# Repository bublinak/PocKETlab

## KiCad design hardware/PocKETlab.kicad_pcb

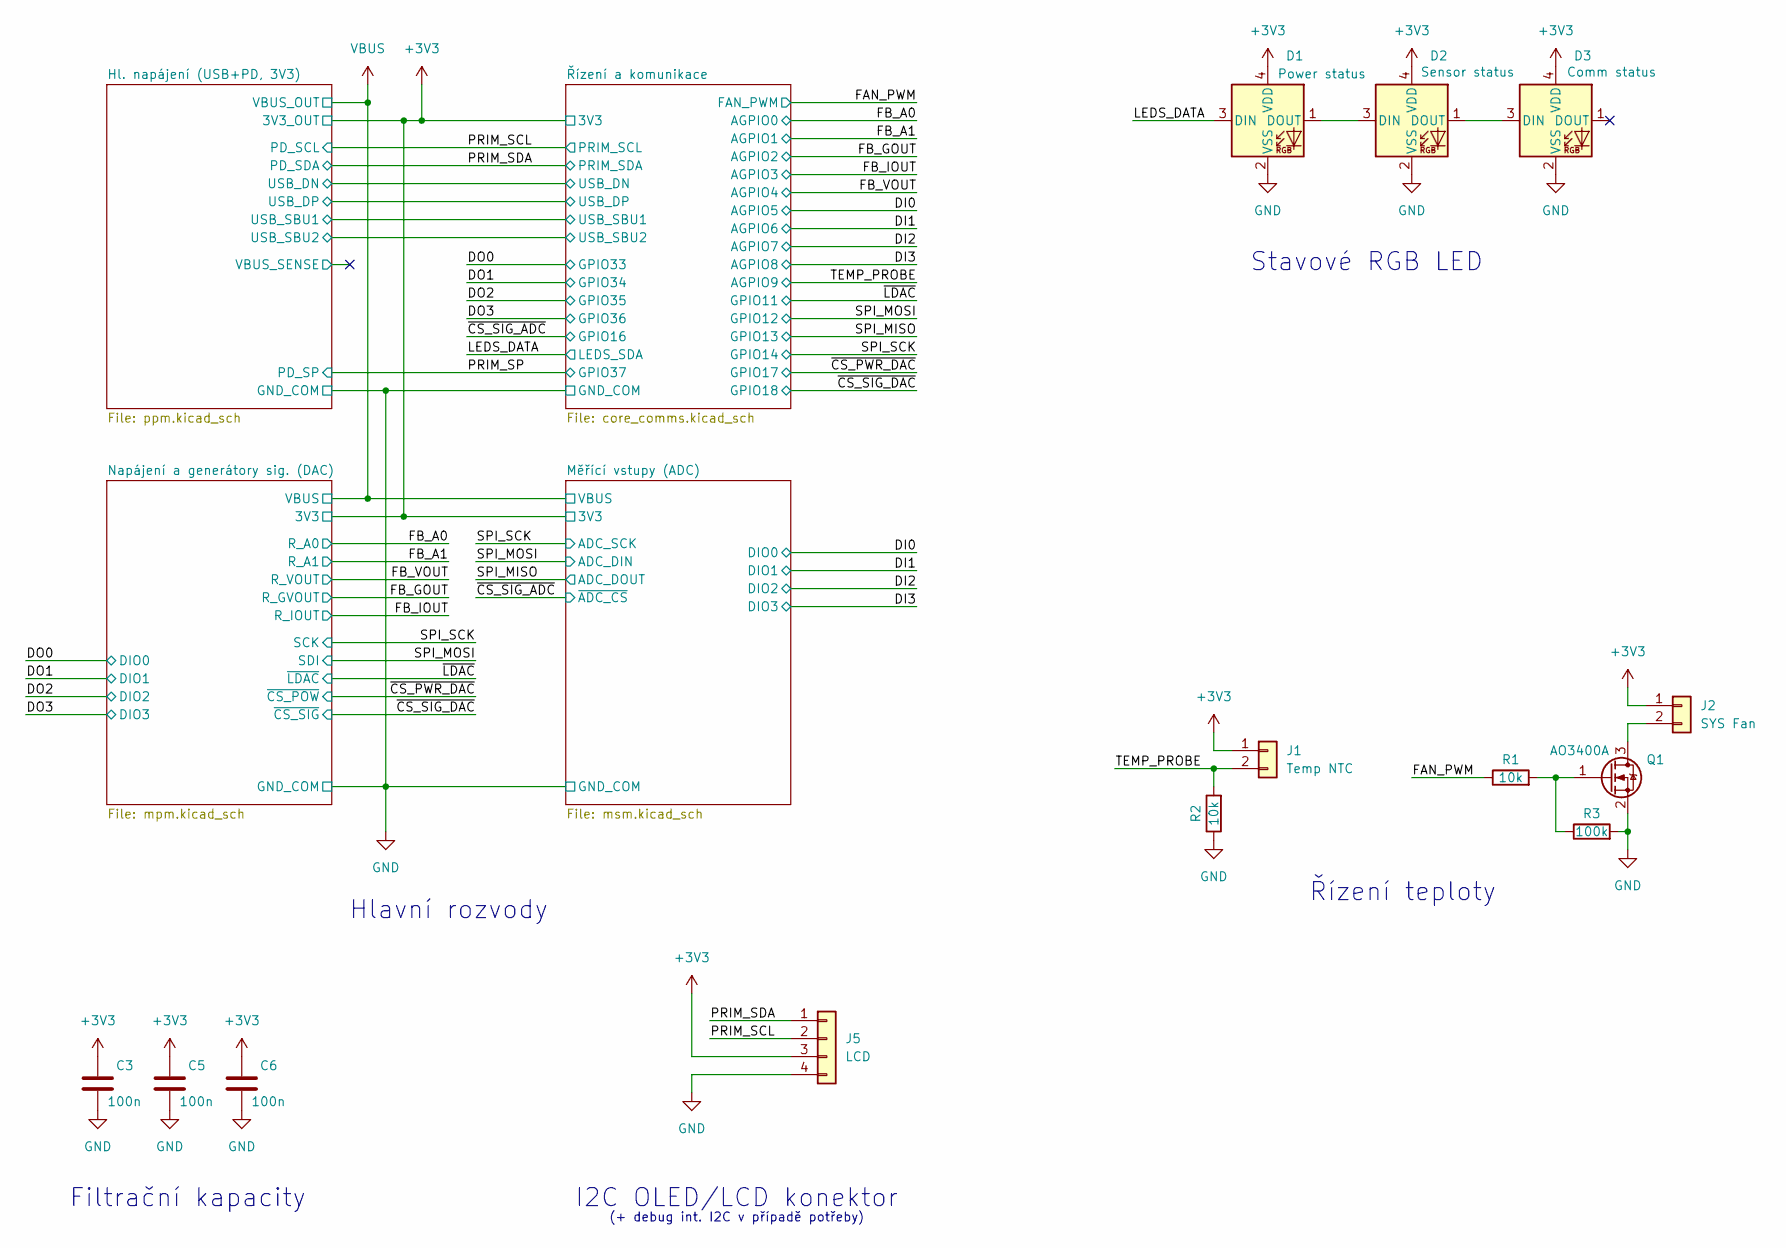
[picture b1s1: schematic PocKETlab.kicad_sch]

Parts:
C3, C5, C6: 100n; C_0603_1608Metric; LCSC Part C14663
D1: Power status; LED_WS2812B-2020_PLCC4_2.0x2.0mm; LCSC Part C5349955
D2: Sensor status; LED_WS2812B-2020_PLCC4_2.0x2.0mm; LCSC Part C5349955
D3: Comm status; LED_WS2812B-2020_PLCC4_2.0x2.0mm; LCSC Part C5349955
J1: Temp NTC; JST_PH_B2B-PH-K_1x02_P2.00mm_Vertical
J2: SYS Fan; JST_PH_B2B-PH-K_1x02_P2.00mm_Vertical
J5: LCD; JST_PH_B4B-PH-K_1x04_P2.00mm_Vertical
Q1: AO3400A; SOT-23; LCSC Part C20917
R1, R2: 10k; R_0603_1608Metric; LCSC Part C25804
R3: 100k; R_0603_1608Metric; LCSC Part C15458

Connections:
+3V3: C3.1, C5.1, C6.1, D1.4 (VDD), D2.4 (VDD), D3.4 (VDD), J1.1, J2.1, J5.3; also elsewhere on the board
/FAN_PWM: R1.1; also elsewhere on the board
/LEDS_DATA: D1.3 (DIN); also elsewhere on the board
/PRIM_SCL: J5.2; also elsewhere on the board
/PRIM_SDA: J5.1; also elsewhere on the board
/TEMP_PROBE: J1.2, R2.2; also elsewhere on the board
GND: C3.2, C5.2, C6.2, D1.2 (VSS), D2.2 (VSS), D3.2 (VSS), J5.4, Q1.2 (S), R2.1, R3.2; also elsewhere on the board
unnamed: D1.1 (DOUT), D2.3 (DIN)
unnamed: D2.1 (DOUT), D3.3 (DIN)
unnamed: J2.2, Q1.3 (D)
unnamed: Q1.1 (G), R1.2, R3.1

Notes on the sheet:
Hlavní rozvody
Řízení teploty
(+ debug int. I2C v případě potřeby)
I2C OLED/LCD konektor
Stavové RGB LED
Filtrační kapacity

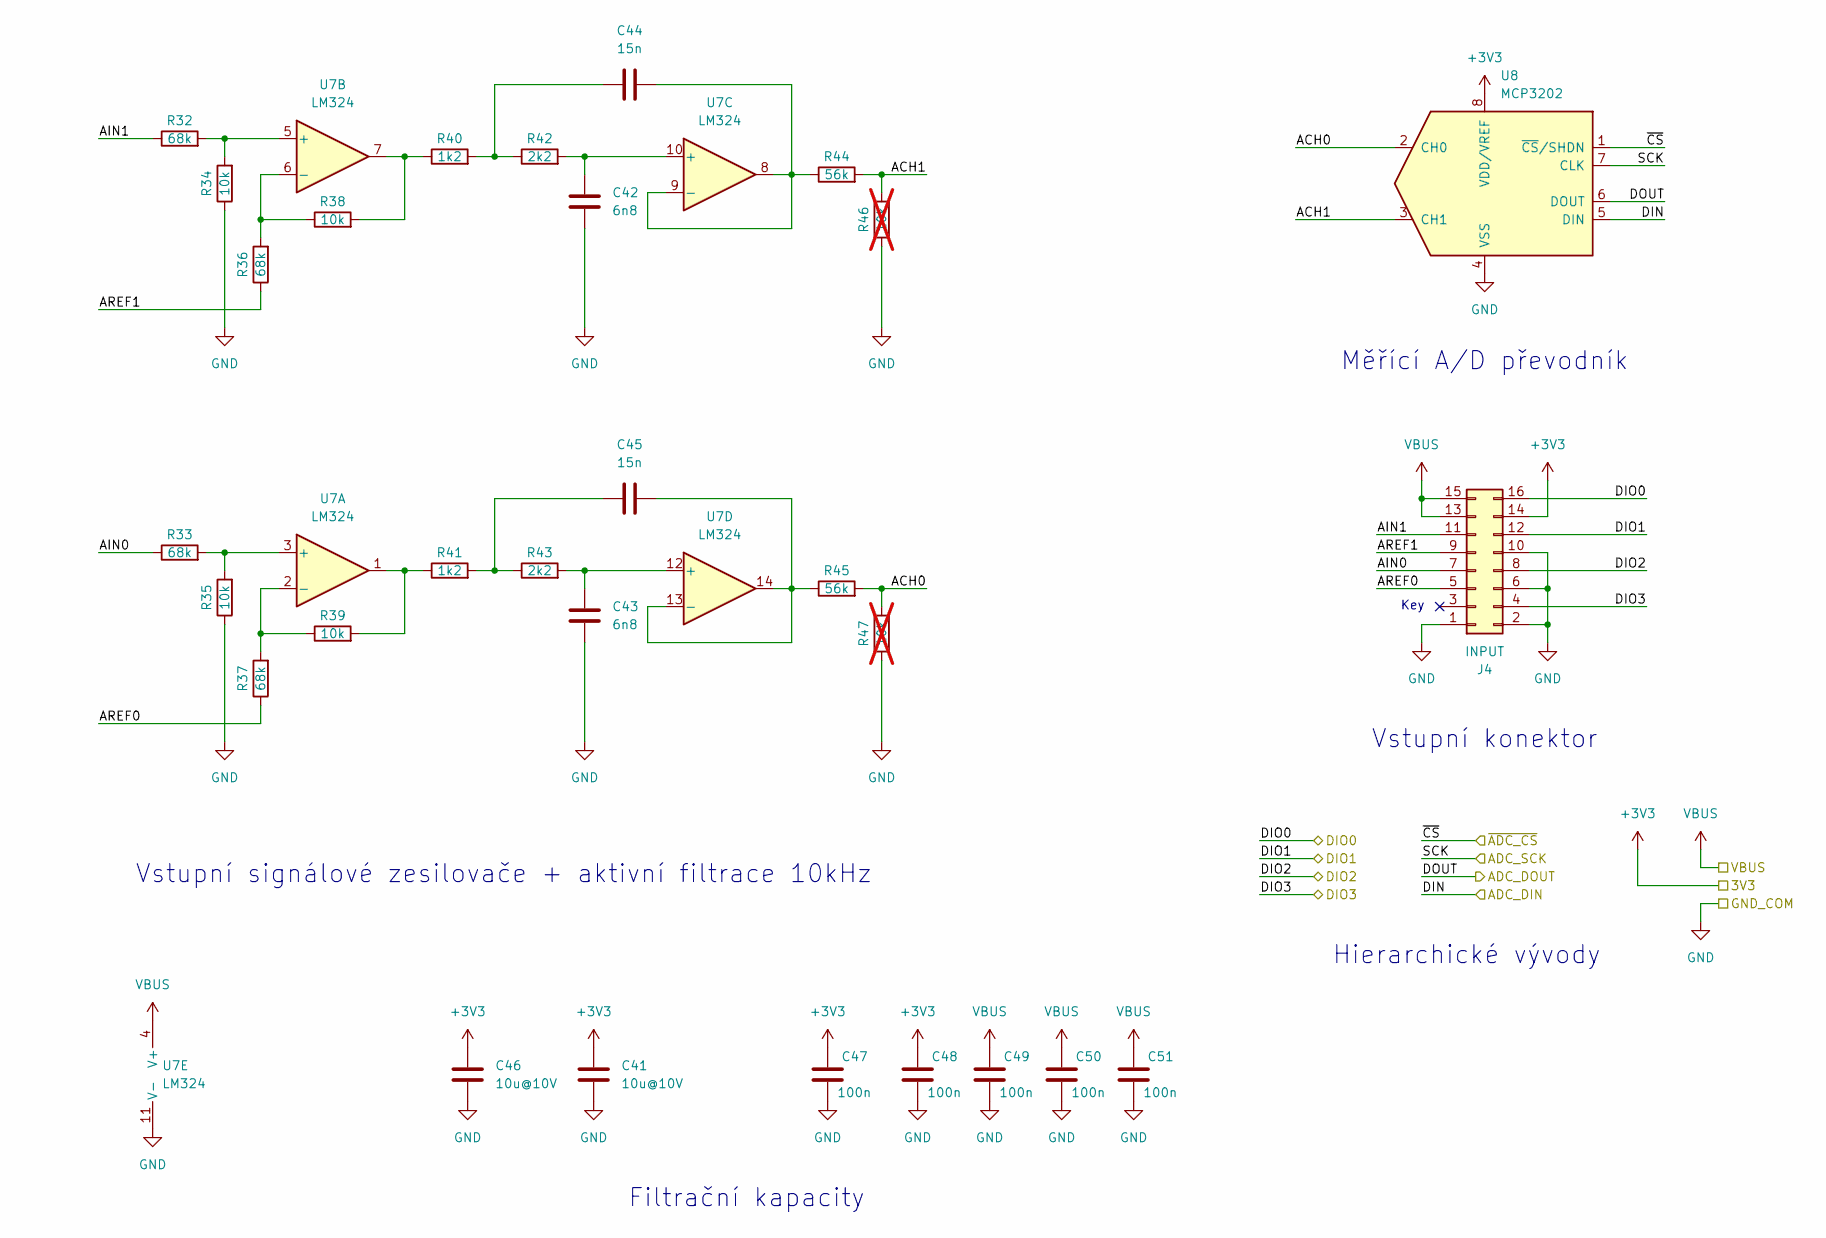
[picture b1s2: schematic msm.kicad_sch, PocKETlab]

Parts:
C41, C46: 10u@10V; C_0603_1608Metric; LCSC Part C96446
C42, C43: 6n8; C_0603_1608Metric; LCSC Part C1631
C44, C45: 15n; C_0603_1608Metric; LCSC Part C1596
C47, C48, C49, C50, C51: 100n; C_0603_1608Metric; LCSC Part C14663
J4: INPUT; PinSocket_2x08_P2.54mm_Vertical_SMD_HOLE; LCSC Part C42163136
R32, R33, R36, R37: 68k; R_0603_1608Metric; LCSC Part C23231
R34, R35, R38, R39: 10k; R_0603_1608Metric; LCSC Part C25804
R40, R41: 1k2; R_0603_1608Metric; LCSC Part C22765
R42, R43: 2k2; R_0603_1608Metric; LCSC Part C4190
R44, R45: 56k; R_0603_1608Metric; LCSC Part C23206
R46, R47: 10k; R_0603_1608Metric; LCSC Part C25804; not fitted
U7: LM324; SOIC-14_3.9x8.7mm_P1.27mm; LCSC Part C7943
U8: MCP3202; SOIC-8_3.9x4.9mm_P1.27mm; LCSC Part C56997

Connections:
+3V3: C41.1, C46.1, C47.1, C48.1, J4.14, U8.8 (VDD/VREF); also elsewhere on the board
/DI0: J4.16; also elsewhere on the board
/DI1: J4.12; also elsewhere on the board
/DI2: J4.8; also elsewhere on the board
/DI3: J4.4; also elsewhere on the board
/Měřící vstupy (ADC)/ACH0: R45.2, R47.2, U8.2 (CH0)
/Měřící vstupy (ADC)/ACH1: R44.2, R46.2, U8.3 (CH1)
/Měřící vstupy (ADC)/AIN0: J4.7, R33.1
/Měřící vstupy (ADC)/AIN1: J4.11, R32.1
/Měřící vstupy (ADC)/AREF0: J4.5, R37.1
/Měřící vstupy (ADC)/AREF1: J4.9, R36.1
/SPI_MISO: U8.6 (DOUT); also elsewhere on the board
/SPI_MOSI: U8.5 (DIN); also elsewhere on the board
/SPI_SCK: U8.7 (CLK); also elsewhere on the board
/~CS_SIG_ADC: U8.1 (~CS/SHDN); also elsewhere on the board
GND: C41.2, C42.2, C43.2, C46.2, C47.2, C48.2, C49.2, C50.2, C51.2, J4.1, J4.2, J4.6, J4.10, R34.1, R35.1, R46.1, R47.1, U7.11 (V-), U8.4 (VSS); also elsewhere on the board
unnamed: C44.1, R40.2, R42.1
unnamed: C45.1, R41.2, R43.1
unnamed: R38.2, R40.1, U7.7
unnamed: R39.2, R41.1, U7.1
unnamed: R33.2, R35.2, U7.3 (+)
unnamed: R37.2, R39.1, U7.2 (-)
unnamed: R32.2, R34.2, U7.5 (+)
unnamed: R36.2, R38.1, U7.6 (-)
unnamed: C42.1, R42.2, U7.10 (+)
unnamed: C44.2, R44.1, U7.8, U7.9 (-)
unnamed: C43.1, R43.2, U7.12 (+)
unnamed: C45.2, R45.1, U7.13 (-), U7.14
VBUS: C49.1, C50.1, C51.1, J4.13, J4.15, U7.4 (V+); also elsewhere on the board

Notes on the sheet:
Hierarchické vývody
Vstupní konektor
Vstupní signálové zesilovače + aktivní filtrace 10kHz
Key
Měřící A/D převodník
Filtrační kapacity

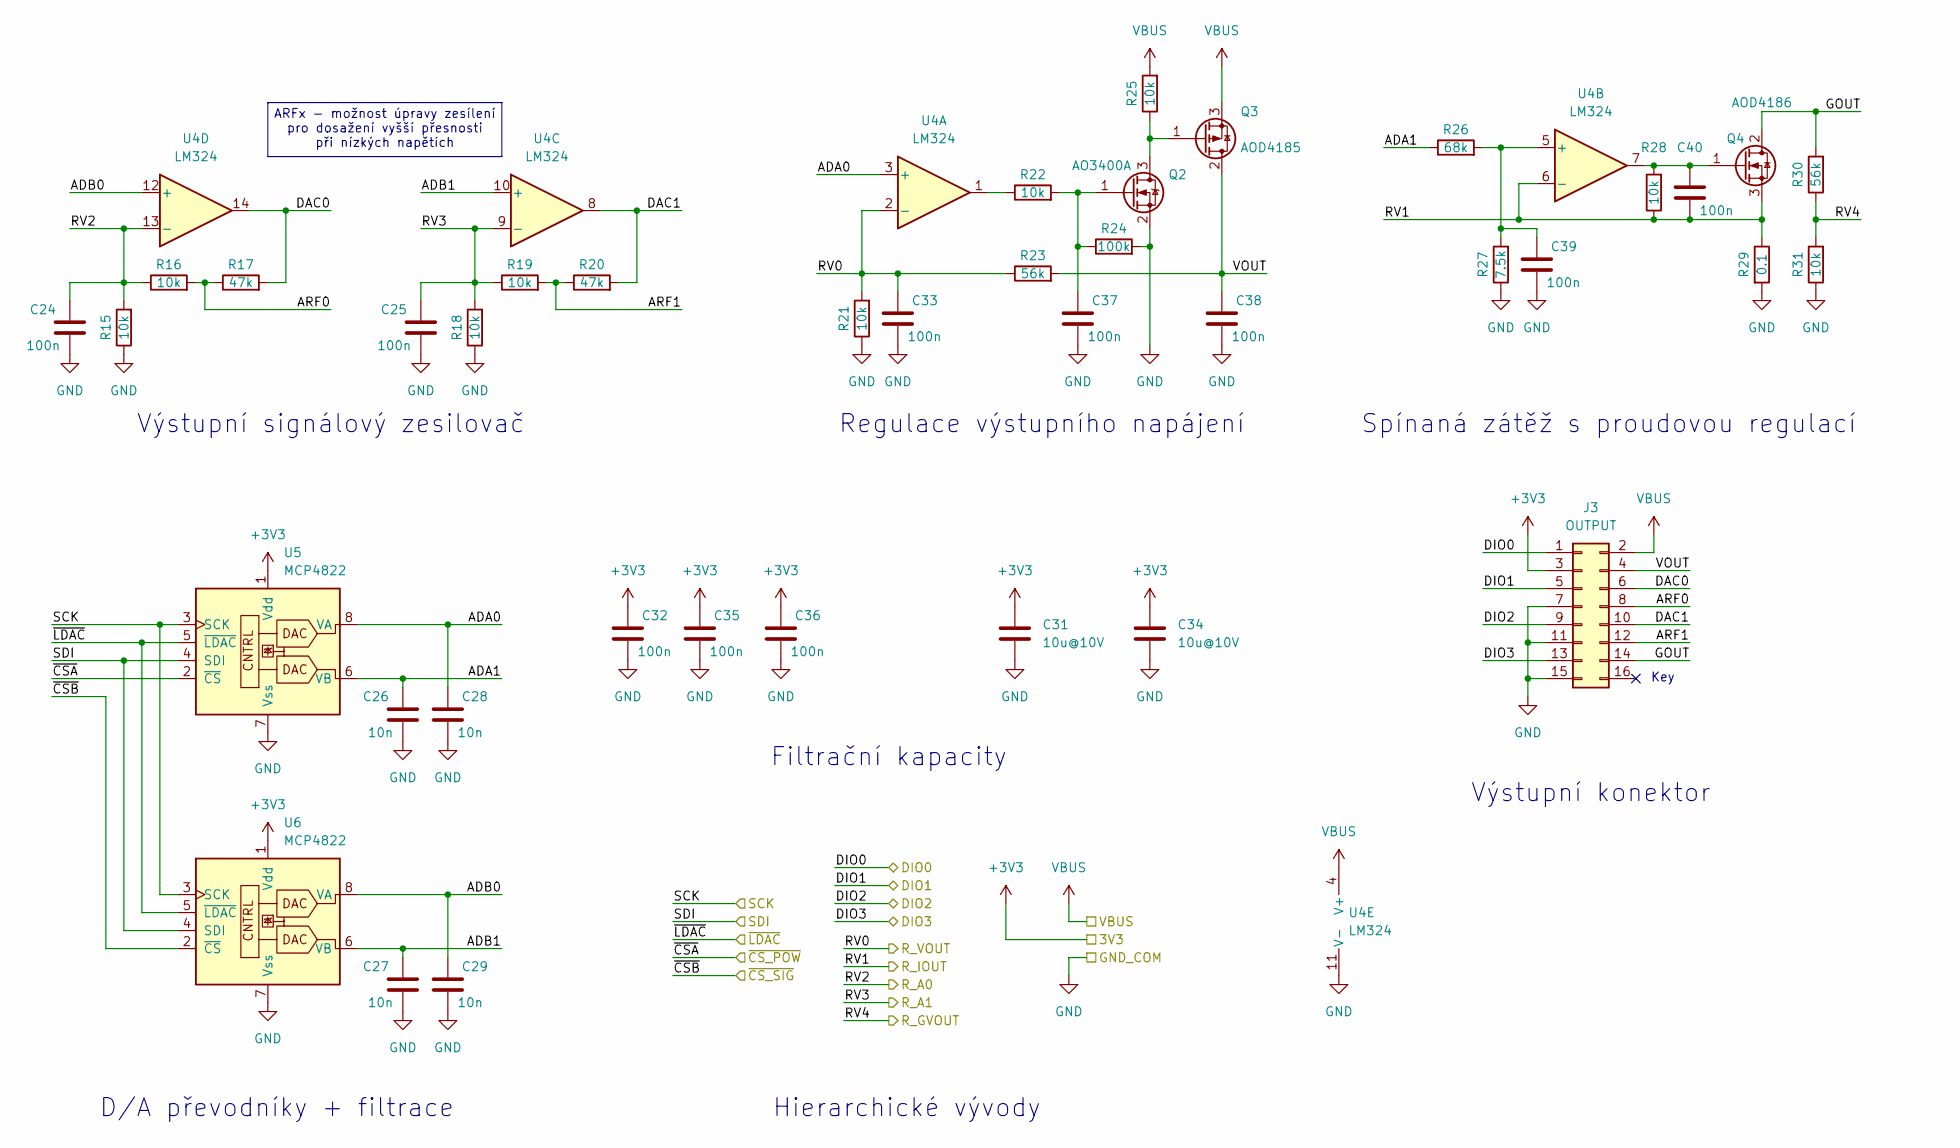
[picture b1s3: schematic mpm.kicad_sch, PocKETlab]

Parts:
C24, C25, C32, C33, C35, C36, C37, C38, C39, C40: 100n; C_0603_1608Metric; LCSC Part C14663
C26, C27, C28, C29: 10n; C_0603_1608Metric; LCSC Part C1588
C31, C34: 10u@10V; C_0603_1608Metric; LCSC Part C96446
J3: OUTPUT; PinSocket_2x08_P2.54mm_Vertical_SMD_HOLE; LCSC Part C42163136
Q2: AO3400A; SOT-23; LCSC Part C20917
Q3: AOD4185; TO-252-2; LCSC Part C77993
Q4: AOD4186; TO-252-2; LCSC Part C111914
R15, R16, R18, R19, R21, R22, R25, R28, R31: 10k; R_0603_1608Metric; LCSC Part C25804
R17, R20: 47k; R_0603_1608Metric; LCSC Part C25819
R23, R30: 56k; R_0603_1608Metric; LCSC Part C23206
R24: 100k; R_0603_1608Metric; LCSC Part C15458
R26: 68k; R_0603_1608Metric; LCSC Part C23231
R27: 7.5k; R_0603_1608Metric; LCSC Part C23234
R29: 0.1; R_1206_3216Metric; LCSC Part C25334
U4: LM324; SOIC-14_3.9x8.7mm_P1.27mm; LCSC Part C7943
U5, U6: MCP4822; SOIC-8_3.9x4.9mm_P1.27mm; LCSC Part C623653

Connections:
+3V3: C31.1, C32.1, C34.1, C35.1, C36.1, J3.3, U5.1 (Vdd), U6.1 (Vdd); also elsewhere on the board
/DO0: J3.1; also elsewhere on the board
/DO1: J3.5; also elsewhere on the board
/DO2: J3.9; also elsewhere on the board
/DO3: J3.13; also elsewhere on the board
/FB_A0: C24.1, R15.2, R16.1, U4.13 (-); also elsewhere on the board
/FB_A1: C25.1, R18.2, R19.1, U4.9 (-); also elsewhere on the board
/FB_GOUT: R30.1, R31.2; also elsewhere on the board
/FB_IOUT: C40.2, Q4.3 (S), R28.1, R29.1, U4.6 (-); also elsewhere on the board
/FB_VOUT: C33.1, R21.2, R23.1, U4.2 (-); also elsewhere on the board
/Napájení a generátory sig. (DAC)/ADA0: C28.1, U4.3 (+), U5.8 (VA)
/Napájení a generátory sig. (DAC)/ADA1: C26.1, R26.1, U5.6 (VB)
/Napájení a generátory sig. (DAC)/ADB0: C29.1, U4.12 (+), U6.8 (VA)
/Napájení a generátory sig. (DAC)/ADB1: C27.1, U4.10 (+), U6.6 (VB)
/Napájení a generátory sig. (DAC)/ARF0: J3.8, R16.2, R17.1
/Napájení a generátory sig. (DAC)/ARF1: J3.12, R19.2, R20.1
/Napájení a generátory sig. (DAC)/DAC0: J3.6, R17.2, U4.14
/Napájení a generátory sig. (DAC)/DAC1: J3.10, R20.2, U4.8
/Napájení a generátory sig. (DAC)/GOUT: J3.14, Q4.2 (D), R30.2
/Napájení a generátory sig. (DAC)/VOUT: C38.1, J3.4, Q3.2 (D), R23.2
/SPI_MOSI: U5.4 (SDI), U6.4 (SDI); also elsewhere on the board
/SPI_SCK: U5.3 (SCK), U6.3 (SCK); also elsewhere on the board
/~CS_PWR_DAC: U5.2 (~CS); also elsewhere on the board
/~CS_SIG_DAC: U6.2 (~CS); also elsewhere on the board
/~LDAC: U5.5 (~LDAC), U6.5 (~LDAC); also elsewhere on the board
GND: C24.2, C25.2, C26.2, C27.2, C28.2, C29.2, C31.2, C32.2, C33.2, C34.2, C35.2, C36.2, C37.2, C38.2, C39.2, J3.7, J3.11, J3.15, Q2.2 (S), R15.1, R18.1, R21.1, R24.2, R27.1, R29.2, R31.1, U4.11 (V-), U5.7 (Vss), U6.7 (Vss); also elsewhere on the board
unnamed: Q2.3 (D), Q3.1 (G), R25.1
unnamed: C37.1, Q2.1 (G), R22.2, R24.1
unnamed: C40.1, Q4.1 (G), R28.2, U4.7
unnamed: R22.1, U4.1
unnamed: C39.1, R26.2, R27.2, U4.5 (+)
VBUS: J3.2, Q3.3 (S), R25.2, U4.4 (V+); also elsewhere on the board

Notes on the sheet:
Regulace výstupního napájení
Hierarchické vývody
Výstupní signálový zesilovač
D/A převodníky + filtrace
Spínaná zátěž s proudovou regulací
ARFx - možnost úpravy zesílení pro dosažení vyšší přesnosti při nízkých napětích
Key
Filtrační kapacity
Výstupní konektor

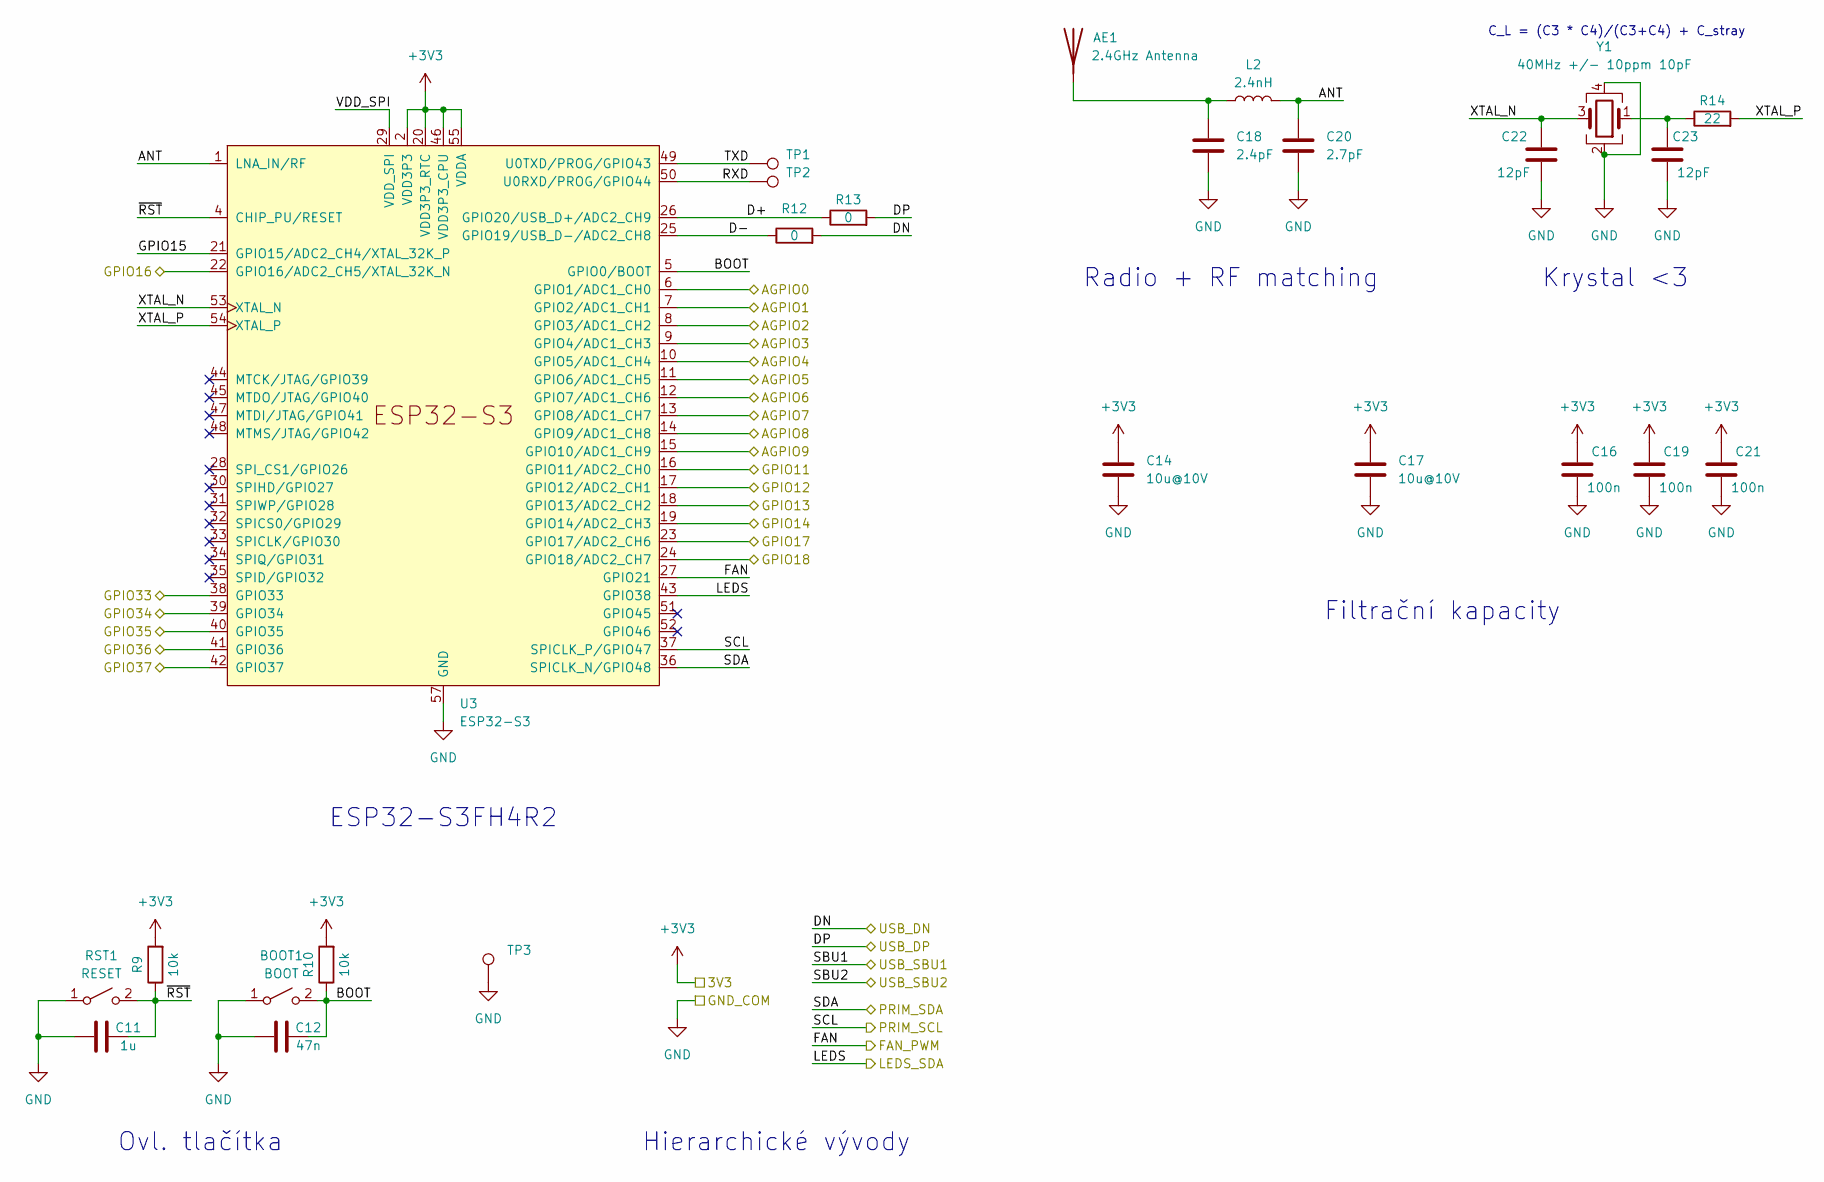
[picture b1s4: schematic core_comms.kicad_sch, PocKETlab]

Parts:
AE1: 2.4GHz Antenna; Johanson_2450AT18x100; LCSC Part C89334
BOOT1: BOOT; SW_Push_1P1T_NO_CK_KMR2; LCSC Part C72443
C11: 1u; C_0603_1608Metric; LCSC Part C15849
C12: 47n; C_0603_1608Metric; LCSC Part C1622
C14, C17: 10u@10V; C_0603_1608Metric; LCSC Part C96446
C16, C19, C21: 100n; C_0603_1608Metric; LCSC Part C14663
C18: 2.4pF; C_0402_1005Metric; LCSC Part C260623
C20: 2.7pF; C_0402_1005Metric; LCSC Part C277484
C22, C23: 12pF; C_0402_1005Metric; LCSC Part C1547
L2: 2.4nH; L_0402_1005Metric; LCSC Part C97997
R9, R10: 10k; R_0603_1608Metric; LCSC Part C25804
R12, R13: 0; R_0402_1005Metric; LCSC Part C17168
R14: 22; R_0402_1005Metric; LCSC Part C25092
RST1: RESET; SW_Push_1P1T_NO_CK_KMR2; LCSC Part C72443
TP1, TP2, TP3: TestPoint; TestPoint_Pad_D1.5mm
U3: ESP32-S3; QFN-56-1EP_7x7mm_P0.4mm_EP5.6x5.6mm; LCSC Part C3013940
Y1: 40MHz +/- 10ppm 10pF; Crystal_SMD_2016-4Pin_2.0x1.6mm; LCSC Part C255898

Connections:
+3V3: C14.1, C16.1, C17.1, C19.1, C21.1, R9.2, R10.2, U3.2 (VDD3P3), U3.3 (VDD3P3), U3.20 (VDD3P3_RTC), U3.46 (VDD3P3_CPU), U3.55 (VDDA), U3.56 (VDDA); also elsewhere on the board
/DI0: U3.11 (GPIO6/ADC1_CH5); also elsewhere on the board
/DI1: U3.12 (GPIO7/ADC1_CH6); also elsewhere on the board
/DI2: U3.13 (GPIO8/ADC1_CH7); also elsewhere on the board
/DI3: U3.14 (GPIO9/ADC1_CH8); also elsewhere on the board
/DO0: U3.38 (GPIO33); also elsewhere on the board
/DO1: U3.39 (GPIO34); also elsewhere on the board
/DO2: U3.40 (GPIO35); also elsewhere on the board
/DO3: U3.41 (GPIO36); also elsewhere on the board
/FAN_PWM: U3.27 (GPIO21); also elsewhere on the board
/FB_A0: U3.6 (GPIO1/ADC1_CH0); also elsewhere on the board
/FB_A1: U3.7 (GPIO2/ADC1_CH1); also elsewhere on the board
/FB_GOUT: U3.8 (GPIO3/ADC1_CH2); also elsewhere on the board
/FB_IOUT: U3.9 (GPIO4/ADC1_CH3); also elsewhere on the board
/FB_VOUT: U3.10 (GPIO5/ADC1_CH4); also elsewhere on the board
/Hl. napájení (USB+PD, 3V3)/DN: R12.2; also elsewhere on the board
/Hl. napájení (USB+PD, 3V3)/DP: R13.2; also elsewhere on the board
/LEDS_DATA: U3.43 (GPIO38); also elsewhere on the board
/PRIM_SCL: U3.37 (SPICLK_P/GPIO47); also elsewhere on the board
/PRIM_SDA: U3.36 (SPICLK_N/GPIO48); also elsewhere on the board
/PRIM_SP: U3.42 (GPIO37); also elsewhere on the board
/SPI_MISO: U3.18 (GPIO13/ADC2_CH2); also elsewhere on the board
/SPI_MOSI: U3.17 (GPIO12/ADC2_CH1); also elsewhere on the board
/SPI_SCK: U3.19 (GPIO14/ADC2_CH3); also elsewhere on the board
/TEMP_PROBE: U3.15 (GPIO10/ADC1_CH9); also elsewhere on the board
/~CS_PWR_DAC: U3.23 (GPIO17/ADC2_CH6); also elsewhere on the board
/~CS_SIG_ADC: U3.22 (GPIO16/ADC2_CH5/XTAL_32K_N); also elsewhere on the board
/~CS_SIG_DAC: U3.24 (GPIO18/ADC2_CH7); also elsewhere on the board
/~LDAC: U3.16 (GPIO11/ADC2_CH0); also elsewhere on the board
/Řízení a komunikace/ANT: C20.1, L2.2, U3.1 (LNA_IN/RF)
/Řízení a komunikace/BOOT: BOOT1.2 (B), C12.1, R10.1, U3.5 (GPIO0/BOOT)
/Řízení a komunikace/D+: R13.1, U3.26 (GPIO20/USB_D+/ADC2_CH9)
/Řízení a komunikace/D-: R12.1, U3.25 (GPIO19/USB_D-/ADC2_CH8)
/Řízení a komunikace/GPIO15: U3.21 (GPIO15/ADC2_CH4/XTAL_32K_P)
/Řízení a komunikace/RXD: TP2.1, U3.50 (U0RXD/PROG/GPIO44)
/Řízení a komunikace/TXD: TP1.1, U3.49 (U0TXD/PROG/GPIO43)
/Řízení a komunikace/VDD_SPI: U3.29 (VDD_SPI)
/Řízení a komunikace/XTAL_N: C22.1, U3.53 (XTAL_N), Y1.3
/Řízení a komunikace/XTAL_P: R14.2, U3.54 (XTAL_P)
/Řízení a komunikace/~RST: C11.1, R9.1, RST1.2 (B), U3.4 (CHIP_PU/RESET)
GND: BOOT1.1 (A), C11.2, C12.2, C14.2, C16.2, C17.2, C18.2, C19.2, C20.2, C21.2, C22.2, C23.2, RST1.1 (A), TP3.1, U3.57 (GND), Y1.2, Y1.4; also elsewhere on the board
unnamed: AE1.1 (A), C18.1, L2.1
unnamed: C23.1, R14.1, Y1.1

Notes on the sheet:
ESP32-S3FH4R2
Ovl. tlačítka
Krystal <3
Hierarchické vývody
Filtrační kapacity
Radio + RF matching
C_L = (C3 * C4)/(C3+C4) + C_stray

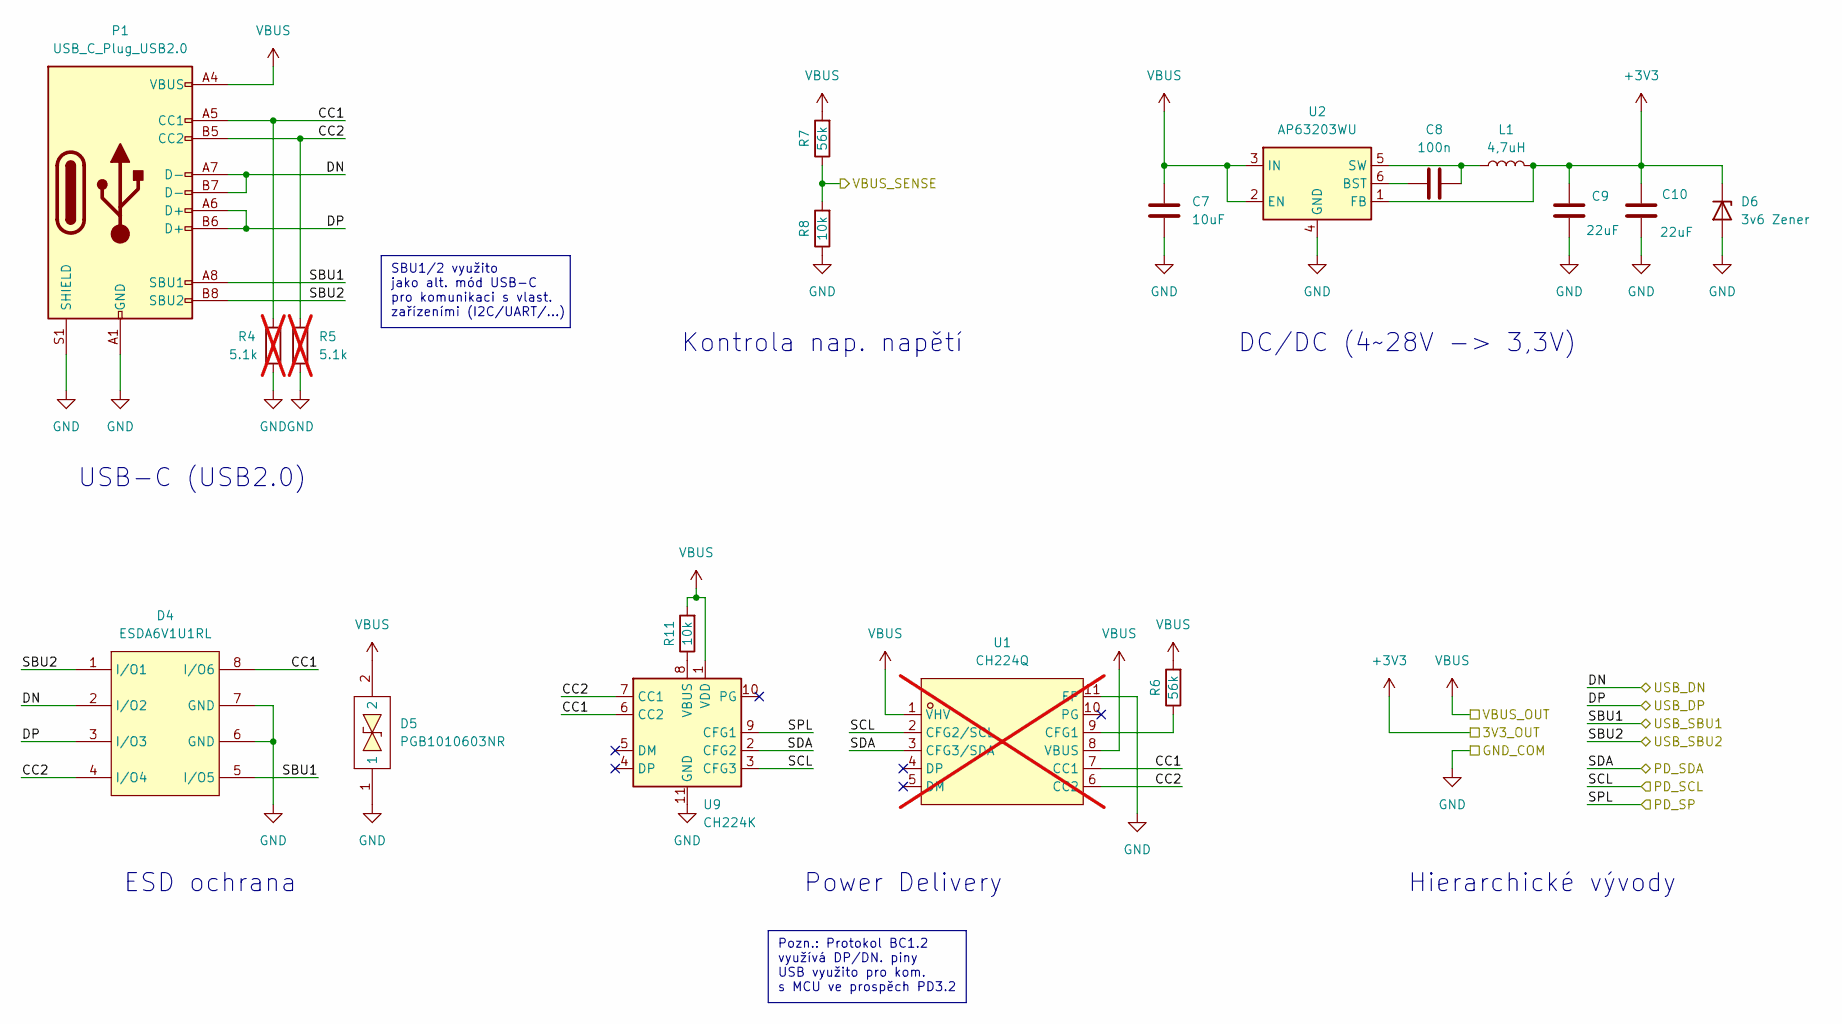
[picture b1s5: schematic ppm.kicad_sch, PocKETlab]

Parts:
C7: 10uF; C_0603_1608Metric; LCSC Part C19702
C8: 100n; C_0603_1608Metric; LCSC Part C14663
C9, C10: 22uF; C_0603_1608Metric; LCSC Part C59461
D4: ESDA6V1U1RL; SO-8_L4.9-W3.9-P1.27-LS5.9-BL; LCSC Part C118278
D5: PGB1010603NR; D0603-BI; LCSC Part C10677
D6: 3v6 Zener; D_SOD-123; LCSC Part C66886
L1: 4,7uH; IND-SMD_L3.5-W3.0; LCSC Part C915148
P1: USB_C_Plug_USB2.0; USB_C_Receptacle_Palconn_UTC16-G; LCSC Part C165948
R4, R5: 5.1k; R_0402_1005Metric; LCSC Part C25905; not fitted
R6, R7: 56k; R_0603_1608Metric; LCSC Part C23206
R8, R11: 10k; R_0603_1608Metric; LCSC Part C25804
U1: CH224Q; DFN-10_L2.0-W2.0-P0.40-BL-EP; LCSC Part C46061833; not fitted
U2: AP63203WU; TSOT-23-6; LCSC Part C780769
U9: CH224K; SSOP-10-1EP_3.9x4.9mm_P1mm_EP2.1x3.3mm

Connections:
+3V3: C9.2, C10.2, D6.1 (K), L1.2, U2.1 (FB); also elsewhere on the board
/Hl. napájení (USB+PD, 3V3)/CC1: D4.8 (I/O6), P1.A5 (CC1), R4.1, U1.7 (CC1), U9.6 (CC2)
/Hl. napájení (USB+PD, 3V3)/CC2: D4.4 (I/O4), P1.B5 (CC2), R5.1, U1.6 (CC2), U9.7 (CC1)
/Hl. napájení (USB+PD, 3V3)/DN: D4.2 (I/O2), P1.A7 (D-), P1.B7 (D-); also elsewhere on the board
/Hl. napájení (USB+PD, 3V3)/DP: D4.3 (I/O3), P1.A6 (D+), P1.B6 (D+); also elsewhere on the board
/Hl. napájení (USB+PD, 3V3)/SBU1: D4.5 (I/O5), P1.A8 (SBU1)
/Hl. napájení (USB+PD, 3V3)/SBU2: D4.1 (I/O1), P1.B8 (SBU2)
/Hl. napájení (USB+PD, 3V3)/VBUS_SENSE: R7.1, R8.2
/PRIM_SCL: U1.2 (CFG2/SCL), U9.3 (CFG3); also elsewhere on the board
/PRIM_SDA: U1.3 (CFG3/SDA), U9.2 (CFG2); also elsewhere on the board
/PRIM_SP: U9.9 (CFG1); also elsewhere on the board
GND: C7.1, C9.1, C10.1, D4.6 (GND), D4.7 (GND), D5.1, D6.2 (A), P1.A1 (GND), P1.A12 (GND), P1.B1 (GND), P1.B12 (GND), P1.S1 (SHIELD), R4.2, R5.2, R8.1, U1.11 (EP), U2.4 (GND), U9.11 (GND); also elsewhere on the board
unnamed: R6.1, U1.9 (CFG1)
unnamed: C8.1, U2.6 (BST)
unnamed: C8.2, L1.1, U2.5 (SW)
unnamed: R11.1, U9.8 (VBUS)
VBUS: C7.2, D5.2, P1.A4 (VBUS), P1.A9 (VBUS), P1.B4 (VBUS), P1.B9 (VBUS), R6.2, R7.2, R11.2, U1.1 (VHV), U1.8 (VBUS), U2.2 (EN), U2.3 (IN), U9.1 (VDD); also elsewhere on the board

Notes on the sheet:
Pozn.: Protokol BC1.2 využívá DP/DN. piny USB využito pro kom. s MCU ve prospěch PD3.2
Hierarchické vývody
USB-C (USB2.0)
SBU1/2 využito jako alt. mód USB-C pro komunikaci s vlast. zařízeními (I2C/UART/...)
DC/DC (4~28V -> 3,3V)
Kontrola nap. napětí
ESD ochrana
Power Delivery

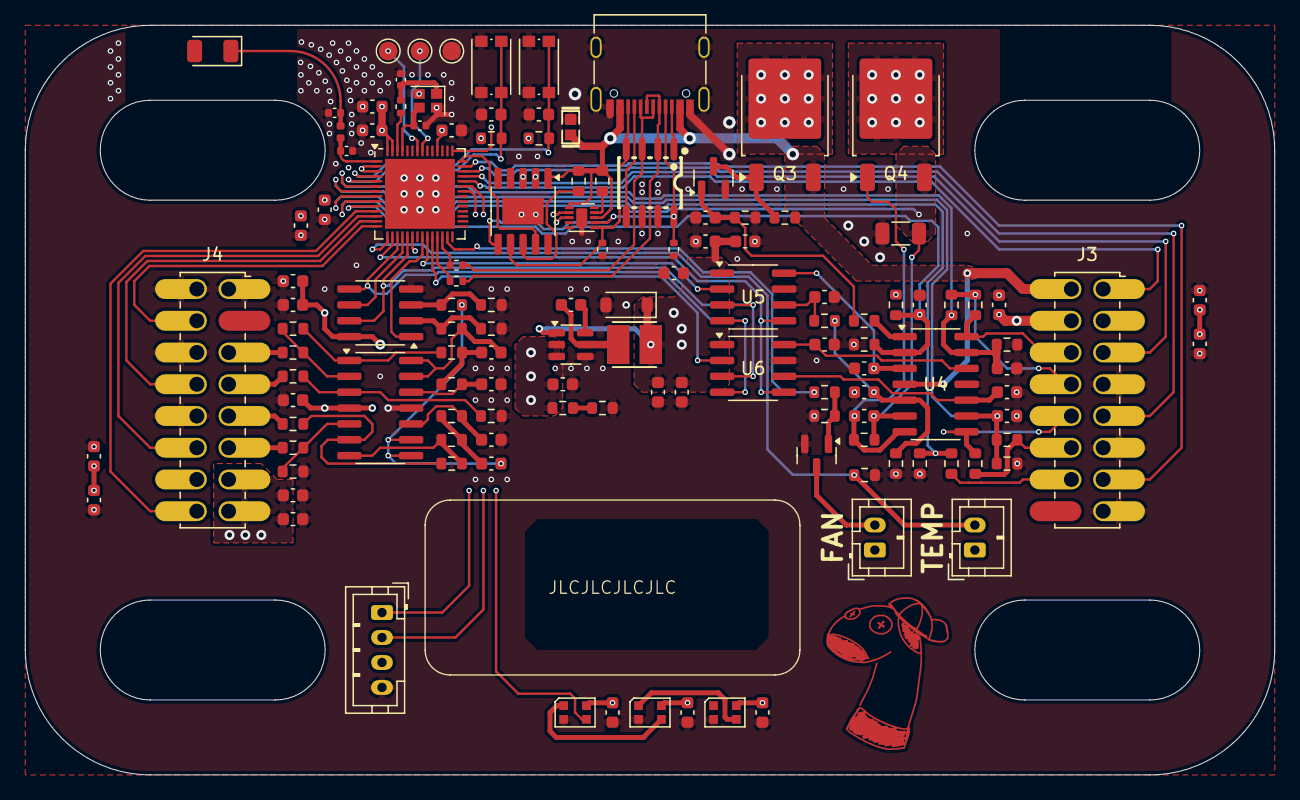
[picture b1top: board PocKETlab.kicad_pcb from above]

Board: 4 copper layers, 100.0 x 60.0 mm, 126 parts (0 on the bottom side), 88 nets.

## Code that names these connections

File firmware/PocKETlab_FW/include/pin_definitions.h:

#ifndef PIN_DEFINITIONS_H
#define PIN_DEFINITIONS_H

// --- System Pins ---
// CHIP_PU/RESET is not a GPIO, but the reset pin.
// GPIO0 is often used for boot mode.
constexpr int PIN_BOOT_BUTTON = 0; // GPIO0, BOOT (Sheet 3, U3 Pin 5)

// --- Analog Feedback & DA/DB General-Purpose I/O (via AGPIO nets on Sheet 1, from ESP32 Sheet 3) ---
// These AGPIOx nets connect to various parts of the system.
// AGPIO0-4 are analog feedback/control lines.
// AGPIO5-8 are general-purpose lines directly on the MCU capable of digital I/O and analog input.
constexpr int PIN_FB_AO = 1;       // GPIO1 -> AGPIO0 -> FB_AO (Sheet 1) - FEEDBACK from DAC0
constexpr int PIN_FB_A1 = 2;       // GPIO2 -> AGPIO1 -> FB_A1 (Sheet 1) - FEEDBACK from DAC1
constexpr int PIN_FB_GOUT = 3;     // GPIO3 -> AGPIO2 -> FB_GOUT (Sheet 1) - FEEDBACK from floating ground (current limiter voltage)
constexpr int PIN_FB_IOUT = 4;     // GPIO4 -> AGPIO3 -> FB_IOUT (Sheet 1) - FEEDBACK from current limiter
constexpr int PIN_FB_VOUT = 5;     // GPIO5 -> AGPIO4 -> FB_VOUT (Sheet 1) - FEEDBACK from voltage output
// Renamed: DAx (Digital/Analog capable) channels (MCU pins; digital I/O + analog input, no analog output)
constexpr int PIN_DA0 = 6;    // GPIO6  -> AGPIO5 -> DA0 (was PIN_DIO0_ADC)
constexpr int PIN_DA1 = 7;    // GPIO7  -> AGPIO6 -> DA1 (was PIN_DIO1_ADC)
constexpr int PIN_DA2 = 8;    // GPIO8  -> AGPIO7 -> DA2 (was PIN_DIO2_ADC)
constexpr int PIN_DA3 = 9;    // GPIO9  -> AGPIO8 -> DA3 (was PIN_DIO3_ADC)

// --- Temperature Sensor ---
constexpr int PIN_TEMP_PROBE = 10; // GPIO10 -> AGPIO9 -> TEMP_PROBE (Sheet 1, J1 NTC)

// --- SPI Bus (for DACs U5, U6 and ADC U8) ---
// Connections traced from ESP32 (Sheet 3) to Sheet 1 nets, then to devices.
constexpr int PIN_DAC_LDAC = 11;    // GPIO11 -> GPIO11 net -> LDAC (Sheet 1, to U5, U6)
constexpr int PIN_SPI_MOSI = 12;    // GPIO12 -> GPIO12 net -> SPI_MOSI (Sheet 1, to U5, U6 SDI; U8 DIN)
constexpr int PIN_SPI_MISO = 13;    // GPIO13 -> GPIO13 net -> SPI_MISO (Sheet 1, from U8 DOUT)
constexpr int PIN_SPI_SCK = 14;     // GPIO14 -> GPIO14 net -> SPI_SCK (Sheet 1, to U5, U6 SCK; U8 CLK)

// --- Chip Selects for SPI Devices ---
// CS_SIG_ADC: ESP32 GPIO16 (Sheet 3, pin 22 XTAL_32K_N/GP1016) -> GP1016 net (Sheet 1) -> CS_SIG_ADC -> U8 CS (Sheet 5)
constexpr int PIN_CS_ADC_SIGNAL = 16;
// CS_PWR_DAC: ESP32 GPIO17 (Sheet 3, pin 23 GP1017) -> GP1017 net (Sheet 1) -> CS_PWR_DAC -> U6 CS (Sheet 4)
constexpr int PIN_CS_DAC_POWER = 17;
// CS_SIG_DAC: ESP32 GPIO18 (Sheet 3, pin 24 GP1018) -> GP1018 net (Sheet 1) -> CS_SIG_DAC -> U5 CS (Sheet 4)
constexpr int PIN_CS_DAC_SIGNAL = 18;

// --- Native USB (ESP32-S3 internal USB controller) ---
// These pins are typically handled by the USB stack.
constexpr int PIN_USB_D_MINUS = 19; // GPIO19 (Sheet 3, U3 Pin 25)
constexpr int PIN_USB_D_PLUS = 20;  // GPIO20 (Sheet 3, U3 Pin 26)

// --- PWM Outputs ---
constexpr int PIN_FAN_PWM = 21; // GPIO21 -> FAN net (Sheet 3) -> FAN_PWMD (Sheet 1, to Q1)

// --- RGB LED Data ---
// GPIO38 is used for LEDS_DATA (WS2812 type signal)
constexpr int PIN_RGB_LED_DATA = 38; // GPIO38 -> LEDS net (Sheet 3) -> LEDS_DATA (Sheet 1, to D1, D2, D3)

// --- Primary I2C Bus (for Power Delivery CH224K and LCD Connector J5) ---
// Note: ESP32-S3 uses GPIO47/48 for these, often associated with SPICLK_P/N if not I2C.
// Here, they are PRIM_SCL/SDA.
constexpr int PIN_I2C_SCL_PRIMARY = 47; // GPIO47 (SPICLK_P) -> SCL net (Sheet 3) -> PRIM_SCL (Sheet 1)
constexpr int PIN_I2C_SDA_PRIMARY = 48; // GPIO48 (SPICLK_N) -> SDA net (Sheet 3) -> PRIM_SDA (Sheet 1)

// --- UART0 (for Programming / Debug) ---
constexpr int PIN_UART_TXD0 = 43; // GPIO43 (U0TXD) (Sheet 3, U3 Pin 49)
constexpr int PIN_UART_RXD0 = 44; // GPIO44 (U0RXD) (Sheet 3, U3 Pin 50)


// --- DB lines (GPIO33-GPIO37) monitoring DAC/Power block signals ---
// These GPIOs on the ESP32 (Sheet 3) are connected to nets (GPIO33-GPIO37)
// which on Sheet 1 are driven by outputs from the DAC and ADC blocks.
// This suggests they might be for monitoring/debugging those signals.

// GPIO33 (Sheet 3, U3 Pin 38) <- net GPIO33 <- DO0 from DAC block (Sheet 1)
// DO0 from DAC block (Sheet 4 hierarchical pin) is SCK of DACs.
constexpr int PIN_DB0 = 33;   // was PIN_DIO0_DAC

// GPIO34 (Sheet 3, U3 Pin 39) <- net GPIO34 <- DO1 from DAC block (Sheet 1)
// DO1 from DAC block (Sheet 4 hierarchical pin) is LDAC of DACs.
constexpr int PIN_DB1 = 34;   // was PIN_DIO1_DAC

// GPIO35 (Sheet 3, U3 Pin 40) <- net GPIO35 <- DO2 from DAC block (Sheet 1)
// DO2 from DAC block (Sheet 4 hierarchical pin) is SDI (MOSI) of DACs.
constexpr int PIN_DB2 = 35;   // was PIN_DIO2_DAC

// GPIO36 (Sheet 3, U3 Pin 41) <- net GPIO36 <- DO3 from DAC block (Sheet 1)
// DO3 from DAC block (Sheet 4 hierarchical pin) is CS_POW (CS for U6 Power DAC).
constexpr int PIN_DB3 = 36;   // was PIN_DIO3_DAC

// GPIO37 (Sheet 3, U3 Pin 42) <- net PRIM_SP <- SPL from Power block (Sheet 1)
constexpr int PIN_PD_SPL = 37;

#endif // PIN_DEFINITIONS_H

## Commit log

2025-05-15 Initial
2025-05-26 cleanup, docs moved to wiki
2025-06-02 big test update before everything falls apart
2025-06-03 dummy data but ok for presentation
2025-07-03 {connection:"ok"}
2025-07-14 cst works by half
2025-11-28 Add testbed grid UI and applet management; update MQTT broker configuration
    - Implemented a responsive grid layout for testbed applets in the web UI.
    - Added functionality for managing applet properties, including gauges, sliders, buttons, and status indicators.
    - Enhanced the applet selection process and updated the UI to reflect selected applet properties.
    - Introduced a dialog for exporting measurement data to CSV with customizable options.
    - Updated the MQTT broker URL to use a public broker for improved connectivity.

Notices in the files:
hardware/PocKETlab.kicad_sch:
Licence: MIT
